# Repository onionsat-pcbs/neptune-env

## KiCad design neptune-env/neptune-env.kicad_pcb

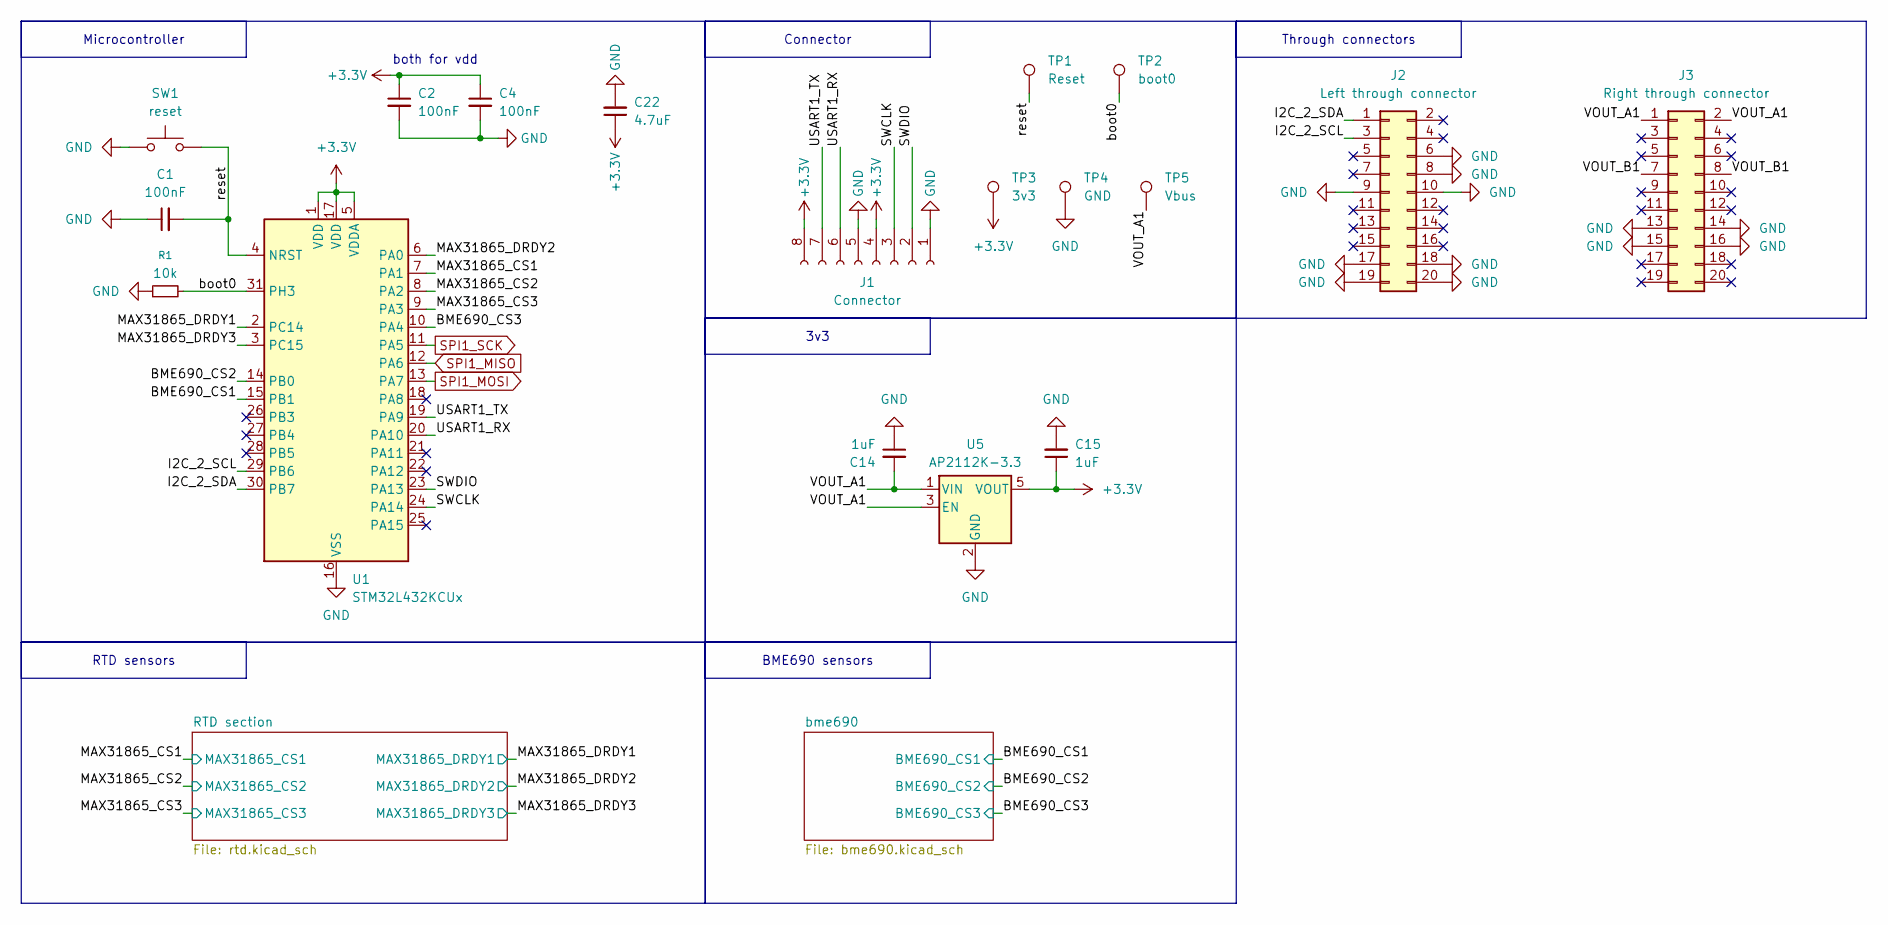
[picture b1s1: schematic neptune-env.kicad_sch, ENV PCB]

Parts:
C1: 100nF; C_0603_1608Metric
C2, C4: 100nF; C_0402_1005Metric
C14, C15: 1uF; C_0603_1608Metric
C22: 4.7uF; C_0603_1608Metric
J1: Connector; HDR-SMD_8P-P2.00-H-F-W9.2
J2: Left through connector; gaia_connector
J3: Right through connector; gaia_connector
R1: 10k; R_0402_1005Metric
SW1: reset; KEY-SMD_L4.0-W3.0-LS4.9-1
TP1: Reset; TestPoint_Pad_1.0x1.0mm
TP2: boot0; TestPoint_Pad_1.0x1.0mm
TP3: 3v3; TestPoint_Pad_1.5x1.5mm
TP4: GND; TestPoint_Pad_1.5x1.5mm
TP5: Vbus; TestPoint_Pad_1.5x1.5mm
U1: STM32L432KCUx
U5: AP2112K-3.3; ap2112

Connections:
+3.3V: C2.1, C4.1, C15.1, C22.1, J1.4, J1.8, TP3.1, U1.1 (VDD), U1.5 (VDDA), U1.17 (VDD), U5.5 (VOUT); also elsewhere on the board
/BME690_CS1: U1.15 (PB1); also elsewhere on the board
/BME690_CS2: U1.14 (PB0); also elsewhere on the board
/BME690_CS3: U1.10 (PA4); also elsewhere on the board
/I2C_2_SCL: J2.3, U1.29 (PB6)
/I2C_2_SDA: J2.1, U1.30 (PB7)
/MAX31865_CS1: U1.7 (PA1); also elsewhere on the board
/MAX31865_CS2: U1.8 (PA2); also elsewhere on the board
/MAX31865_CS3: U1.9 (PA3); also elsewhere on the board
/MAX31865_DRDY1: U1.2 (PC14); also elsewhere on the board
/MAX31865_DRDY2: U1.6 (PA0); also elsewhere on the board
/MAX31865_DRDY3: U1.3 (PC15); also elsewhere on the board
/SWCLK: J1.3, U1.24 (PA14)
/SWDIO: J1.2, U1.23 (PA13)
/USART1_RX: J1.6, U1.20 (PA10)
/USART1_TX: J1.7, U1.19 (PA9)
/VOUT_A1: C14.2, J3.1, J3.2, TP5.1, U5.1 (VIN), U5.3 (EN)
/VOUT_B1: J3.7, J3.8
/boot0: R1.2, TP2.1, U1.31 (PH3)
/reset: C1.2, SW1.2, TP1.1, U1.4 (NRST)
GND: C1.1, C2.2, C4.2, C14.1, C15.2, C22.2, J1.1, J1.5, J2.6, J2.8, J2.9, J2.10, J2.17, J2.18, J2.19, J2.20, J3.13, J3.14, J3.15, J3.16, R1.1, SW1.1, TP4.1, U1.16 (VSS), U1.32 (VSS), U1.33 (VSS), U5.2 (GND); also elsewhere on the board
SPI1_MISO: U1.12 (PA6); also elsewhere on the board
SPI1_MOSI: U1.13 (PA7); also elsewhere on the board
SPI1_SCK: U1.11 (PA5); also elsewhere on the board

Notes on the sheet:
both for vdd
Connector
Through connectors
Microcontroller
BME690 sensors
RTD sensors
3v3

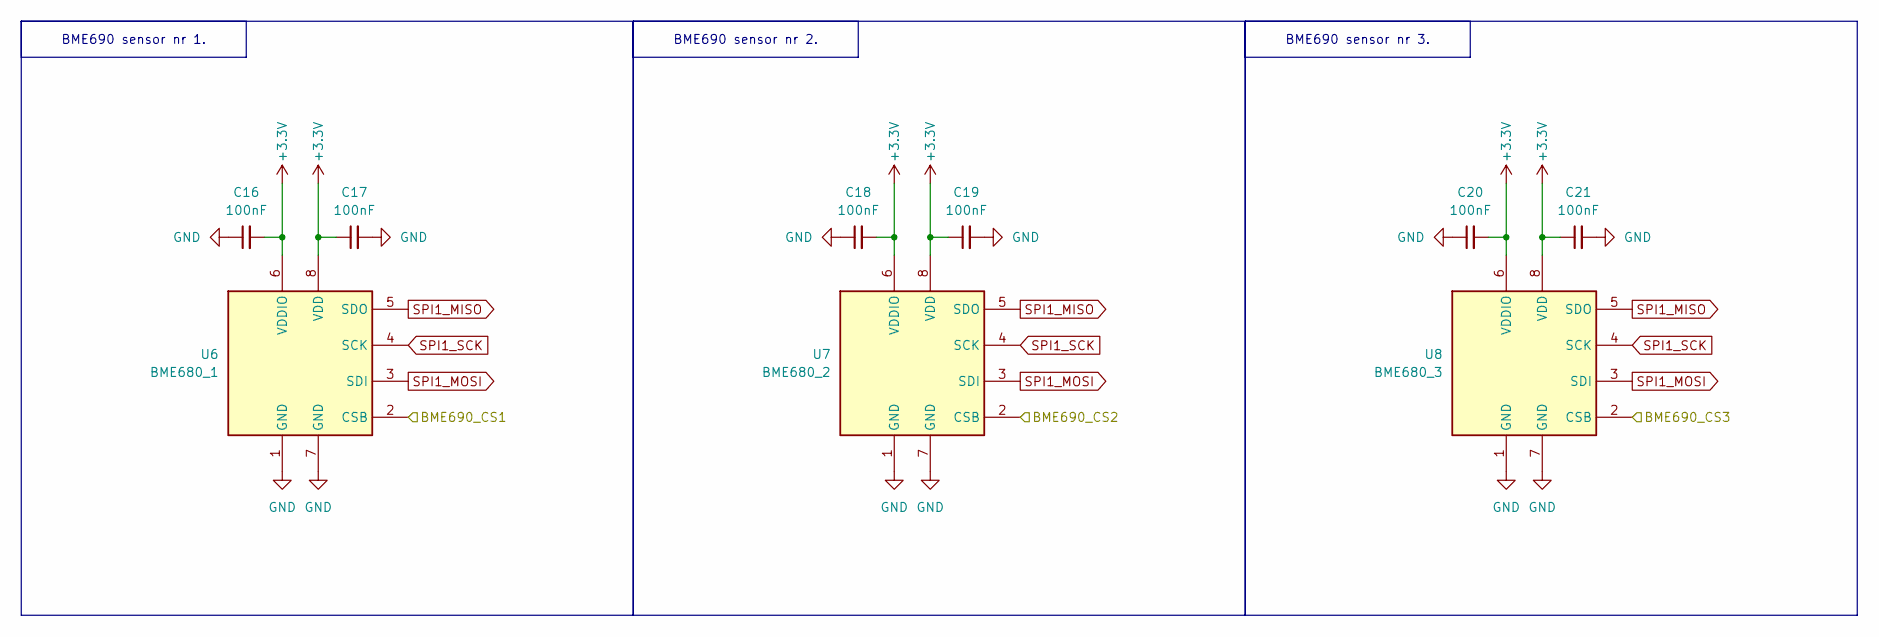
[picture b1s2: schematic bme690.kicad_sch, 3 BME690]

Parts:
C16, C17, C18, C19, C20, C21: 100nF; C_0402_1005Metric
U6: BME680_1; Bosch_LGA-8_3x3mm_P0.8mm_ClockwisePinNumbering
U7: BME680_2; Bosch_LGA-8_3x3mm_P0.8mm_ClockwisePinNumbering
U8: BME680_3; Bosch_LGA-8_3x3mm_P0.8mm_ClockwisePinNumbering

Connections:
+3.3V: C16.2, C17.1, C18.2, C19.1, C20.2, C21.1, U6.6 (VDDIO), U6.8 (VDD), U7.6 (VDDIO), U7.8 (VDD), U8.6 (VDDIO), U8.8 (VDD); also elsewhere on the board
/BME690_CS1: U6.2 (CSB); also elsewhere on the board
/BME690_CS2: U7.2 (CSB); also elsewhere on the board
/BME690_CS3: U8.2 (CSB); also elsewhere on the board
GND: C16.1, C17.2, C18.1, C19.2, C20.1, C21.2, U6.1 (GND), U6.7 (GND), U7.1 (GND), U7.7 (GND), U8.1 (GND), U8.7 (GND); also elsewhere on the board
SPI1_MISO: U6.5 (SDO), U7.5 (SDO), U8.5 (SDO); also elsewhere on the board
SPI1_MOSI: U6.3 (SDI), U7.3 (SDI), U8.3 (SDI); also elsewhere on the board
SPI1_SCK: U6.4 (SCK), U7.4 (SCK), U8.4 (SCK); also elsewhere on the board

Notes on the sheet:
BME690 sensor nr 3.
BME690 sensor nr 1.
BME690 sensor nr 2.

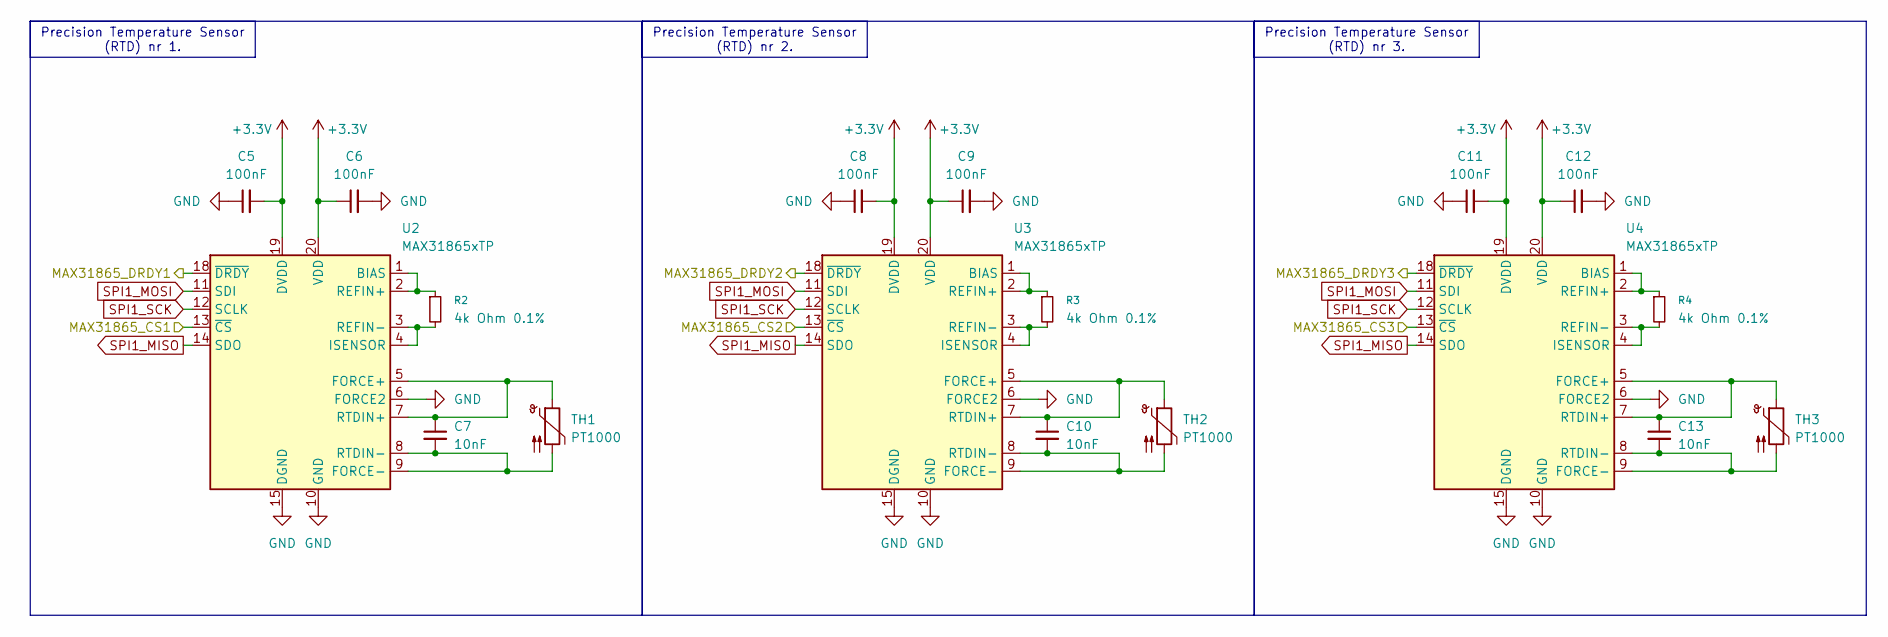
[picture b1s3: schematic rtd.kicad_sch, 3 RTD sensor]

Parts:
C5, C6, C8, C9, C11, C12: 100nF; C_0201_0603Metric
C7, C10, C13: 10nF; C_0402_1005Metric
R2, R3, R4: 4k Ohm 0.1%; R_1206_3216Metric
TH1, TH2, TH3: PT1000; yageo_m1020
U2, U3, U4: MAX31865xTP; MAX31865

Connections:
+3.3V: C5.2, C6.1, C8.2, C9.1, C11.2, C12.1, U2.19 (DVDD), U2.20 (VDD), U3.19 (DVDD), U3.20 (VDD), U4.19 (DVDD), U4.20 (VDD); also elsewhere on the board
/MAX31865_CS1: U2.13 (~CS); also elsewhere on the board
/MAX31865_CS2: U3.13 (~CS); also elsewhere on the board
/MAX31865_CS3: U4.13 (~CS); also elsewhere on the board
/MAX31865_DRDY1: U2.18 (~DRDY); also elsewhere on the board
/MAX31865_DRDY2: U3.18 (~DRDY); also elsewhere on the board
/MAX31865_DRDY3: U4.18 (~DRDY); also elsewhere on the board
GND: C5.1, C6.2, C8.1, C9.2, C11.1, C12.2, U2.6 (FORCE2), U2.10 (GND), U2.15 (DGND), U2.16 (GND), U2.21 (GND), U3.6 (FORCE2), U3.10 (GND), U3.15 (DGND), U3.16 (GND), U3.21 (GND), U4.6 (FORCE2), U4.10 (GND), U4.15 (DGND), U4.16 (GND), U4.21 (GND); also elsewhere on the board
unnamed: R2.1, U2.1 (BIAS), U2.2 (REFIN+)
unnamed: C7.1, TH1.1, U2.5 (FORCE+), U2.7 (RTDIN+)
unnamed: C7.2, TH1.2, U2.8 (RTDIN-), U2.9 (FORCE-)
unnamed: R2.2, U2.3 (REFIN-), U2.4 (ISENSOR)
unnamed: R3.1, U3.1 (BIAS), U3.2 (REFIN+)
unnamed: C10.1, TH2.1, U3.5 (FORCE+), U3.7 (RTDIN+)
unnamed: C10.2, TH2.2, U3.8 (RTDIN-), U3.9 (FORCE-)
unnamed: R3.2, U3.3 (REFIN-), U3.4 (ISENSOR)
unnamed: R4.1, U4.1 (BIAS), U4.2 (REFIN+)
unnamed: C13.1, TH3.1, U4.5 (FORCE+), U4.7 (RTDIN+)
unnamed: C13.2, TH3.2, U4.8 (RTDIN-), U4.9 (FORCE-)
unnamed: R4.2, U4.3 (REFIN-), U4.4 (ISENSOR)
SPI1_MISO: U2.14 (SDO), U3.14 (SDO), U4.14 (SDO); also elsewhere on the board
SPI1_MOSI: U2.11 (SDI), U3.11 (SDI), U4.11 (SDI); also elsewhere on the board
SPI1_SCK: U2.12 (SCLK), U3.12 (SCLK), U4.12 (SCLK); also elsewhere on the board

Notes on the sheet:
Precision Temperature Sensor (RTD) nr 3.
Precision Temperature Sensor (RTD) nr 2.
Precision Temperature Sensor (RTD) nr 1.

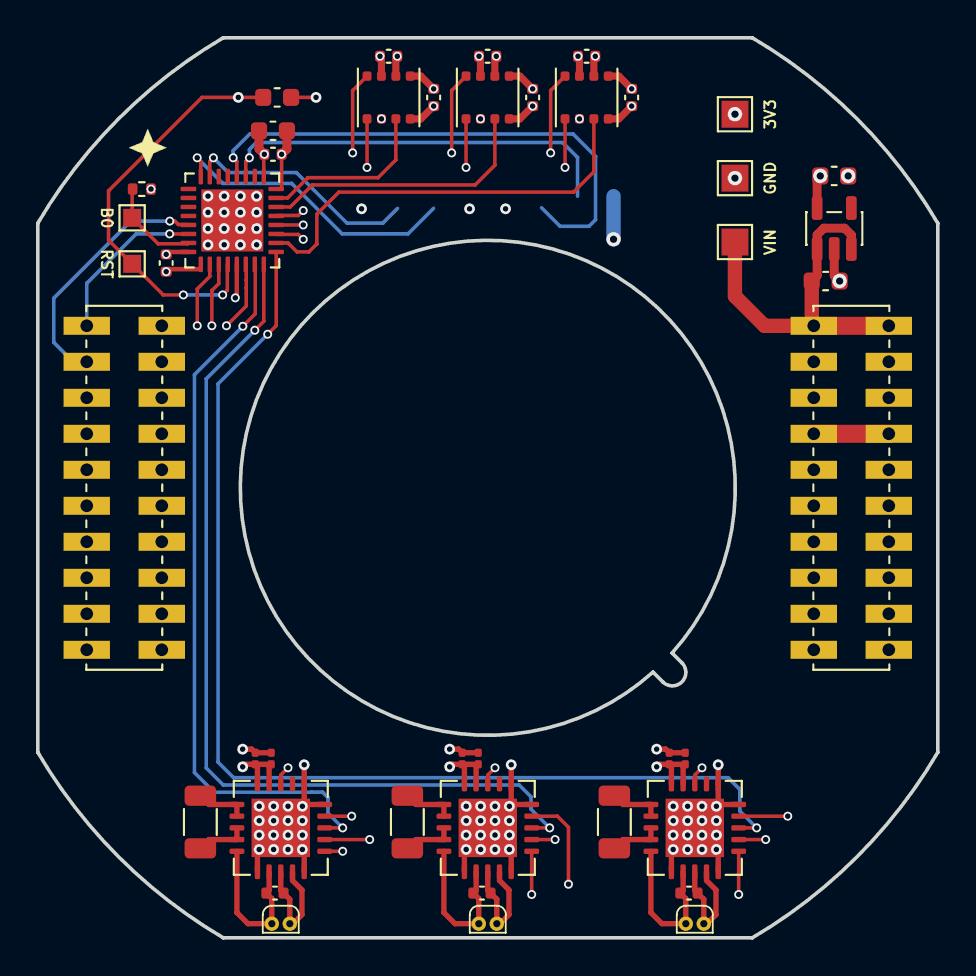
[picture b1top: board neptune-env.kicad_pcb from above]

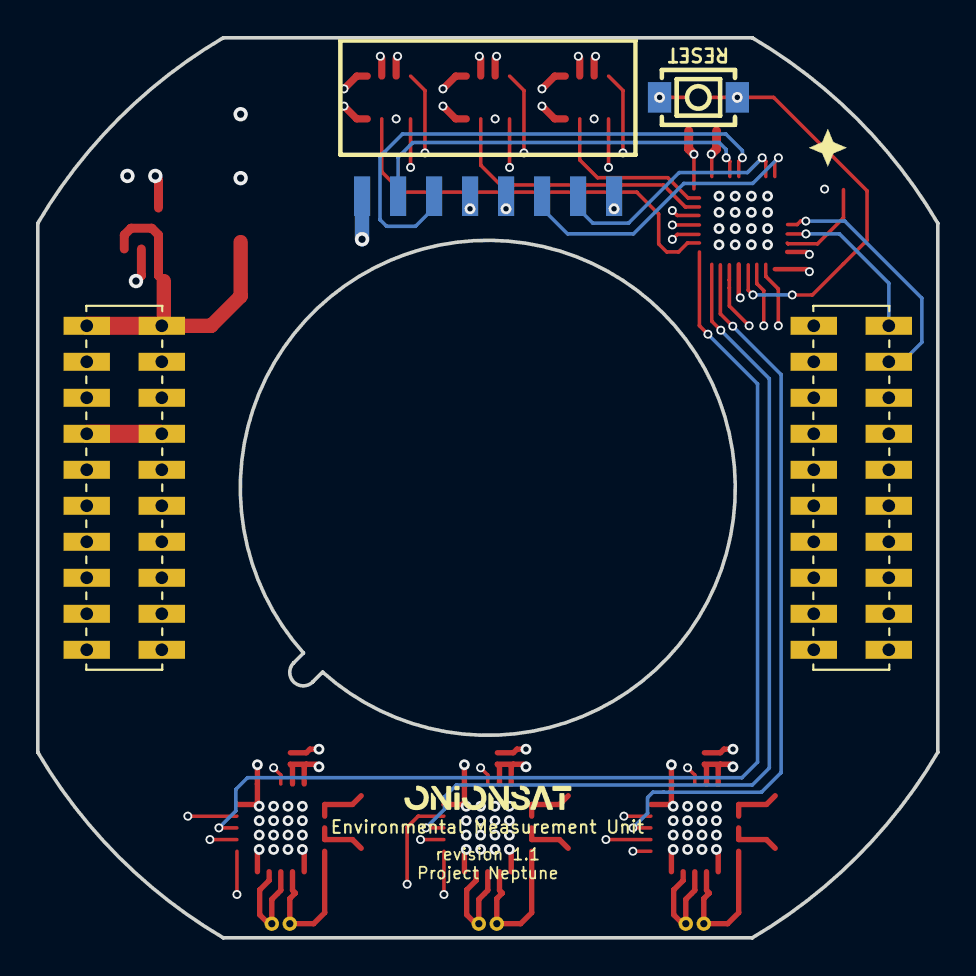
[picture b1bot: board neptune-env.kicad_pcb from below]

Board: 6 copper layers, 50.0 x 50.0 mm, 45 parts (2 on the bottom side), 36 nets.

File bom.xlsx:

Reference | Qty | Name/value | Footprint
C1 | 1 | 100nF | Capacitor_SMD:C_0603_1608Metric
C2,C4,C16,C17,C18,C19,C20,C21 | 8 | 100nF | Capacitor_SMD:C_0402_1005Metric
C5,C6,C8,C9,C11,C12 | 6 | 100nF | Capacitor_SMD:C_0201_0603Metric
C7,C10,C13 | 3 | 10nF | Capacitor_SMD:C_0402_1005Metric
C14,C15 | 2 | 1uF | Capacitor_SMD:C_0603_1608Metric
C22 | 1 | 4.7uF | Capacitor_SMD:C_0603_1608Metric
J1 | 1 | 8 pin, 2mm ptich, SMD, right angle socket | -
J2 | 1 | Neptune 2x10 connector, 1 female, 1 male | -
J3 | 1 | Neptune 2x10 connector, 1 female, 1 male | -
R1 | 1 | 10k | Resistor_SMD:R_0402_1005Metric
R2,R3,R4 | 3 | 4k Ohm 0.1% | Resistor_SMD:R_1206_3216Metric
SW1 | 1 | reset | -
TH1,TH2,TH3 | 3 | PT1000 | -
U1 | 1 | STM32L432KCUx | -
U2,U3,U4 | 3 | MAX31865xTP | -
U5 | 1 | AP2112K-3.3 | -
U6,U7,U8 | 3 | BME690 | -

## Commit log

2025-12-08 Update project title in README
2025-12-08 initial relase
2025-12-09 no summary
2025-12-11 almost ready
2025-12-11 project naming updated
2025-12-11 updating readme.md
2025-12-11 some advancements
2025-12-16 some final things to do
2025-12-16 ready
    final check needed
2025-12-16 unused documents removed
2025-12-17 working on my PC
2025-12-17 ready
2025-12-18 Review: OK for production
2025-12-21 fixing bugs, production
2026-01-07 3D modell fixek
2026-01-26 v1.1 - PRODUCTION
    Header FIX
